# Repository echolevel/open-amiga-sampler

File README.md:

# OPEN AMIGA SAMPLER

## Open source schematics, parts lists and documentation for building a generic 8bit/mono Amiga parallel port sound sampler

Amiga parallel port sound samplers are simple hardware devices from the late 80s/early 90s which allowed users to digitally record audio to their home computer and represented a revolution in DIY music production. They were once cheap and ubiquitous, but they're increasingly expensive and hard to find as the popularity of retro computing continues to rise.

OAS is an open source PCB and case design for a cartridge-style mono sampler geared towards use with Soundtracker and Protracker-style software. It is easy to make, cheap to produce, and thanks to its built in preamp with hardware gain control it can deliver higher quality results than the average vintage sampler.

Please read the wiki for more information!

### [OAS Wiki Home](https://github.com/echolevel/open-amiga-sampler/wiki)

### Background

***
* [What are Amiga samplers?](https://github.com/echolevel/open-amiga-sampler/wiki/What-are-Amiga-samplers%3F)
* [Why build more?](https://github.com/echolevel/open-amiga-sampler/wiki/Why-build-more%3F)

### Development

***
* [How do they work?](https://github.com/echolevel/open-amiga-sampler/wiki/How-do-they-work%3F)
* [⚠️ WARNING](https://github.com/echolevel/open-amiga-sampler/wiki/%E2%9A%A0%EF%B8%8F-WARNING)
* [That WARNING sounds serious. How did you test your design without risking Amiga hardware?](https://github.com/echolevel/open-amiga-sampler/wiki/That-WARNING-sounds-serious.-How-did-you-test-your-design-without-risking-your-Amiga-hardware%3F)
* [Why is this sampler design mono, not stereo?](https://github.com/echolevel/open-amiga-sampler/wiki/Why-is-this-sampler-design-mono,-not-stereo%3F)
* [What's the aim in terms of quality and application?](https://github.com/echolevel/open-amiga-sampler/wiki/What's-the-aim-in-terms-of-quality-and-application%3F)
* [What about those edge cases? Who is OAS not aimed at?](https://github.com/echolevel/open-amiga-sampler/wiki/What-about-those-edge-cases%3F-Who-is-OAS-not-aimed-at%3F)
* [How compatible is OAS with existing software? (Work in progress, submissions welcome)](https://github.com/echolevel/open-amiga-sampler/wiki/How-compatible-is-OAS-with-existing-software%3F-(Work-in-progress,-submissions-welcome))
* [Current status](https://github.com/echolevel/open-amiga-sampler/wiki/Current-status)

### Production & Availability

***
* [Availability](https://github.com/echolevel/open-amiga-sampler/wiki/Availability)
* [DIY assembly](https://github.com/echolevel/open-amiga-sampler/wiki/DIY-assembly)

### Appendices

***
* [Appendix A: Sample rates deep-dive](https://github.com/echolevel/open-amiga-sampler/wiki/Appendix-A:-Sample-rates-deep-dive)
* [Appendix B: Sampling duration deep-dive](https://github.com/echolevel/open-amiga-sampler/wiki/Appendix-B:-Sampling-duration-deep-dive)

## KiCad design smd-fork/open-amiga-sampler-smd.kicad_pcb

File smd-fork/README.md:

# OPEN AMIGA SAMPLER

## Overview

Here you can find the schematic and a PCB layout for Open Amiga Sampler in KiCAD format. Additionally, the schematic is available as a PDF.

The design consists of an inverting opamp circuit with variable gain which feeds an ADC. The DB25's strobe pin is connected to the ADC and initiates a conversion when it goes low. The ADC's outputs are connected to the data pins of a DB25 connector, which also provides power and ground. 

## BOM

* 1x Maxim ADC0820CCM+ (SOIC-20 Package) - mouser P/N  700-ADC0820CCM
* 1x Microchip MCP6001UT-I/OT (SOT-23-5 package) - mouser P/N 579-MCP6001UT-I/OT (The U variant is important as it has a different pin layout to the 6001T in the same package)
* 1x DB25 plug connector
* 2x RCA receptacles
* 1x 0805 330ohm resistor 
* 5x 0805 1kohm resistors
* 1x 10kohm exponential potentimeter
* 1x 4x5.3mm 47uF electrolytic capacitor
* 2x 10uf Tantalum Case A or 1206 capacitors
* 2x 0805 0.1uf capacitors

### Substitutions

The Maxim ADC0820CCM+ is pin compatible with the TI part with the same part number and package. The Maxim part is preferred as it's a better spec but the TI part can easily be substituted as the Maxim is pin-compatible.

The 10kohm potentiometer will give between 1x and 10x gain. A larger potentiometer can be substituted to enable a large maxium gain. The RCA receptacles can be replaced by a stereo jack receptacle if preferred. It is likely that both ICs could be substituted for similar chips with identical pinouts, but these are the models that we have tested and confirmed to work.

The 47uF electrolytic can be substituted for a taller one up to 5.8mm if using a standard grey DB25 shell or taller if using a bigger (e.g. 3D printed) case 

## Soldering

All on board components are surface mount but nothing smaller than 0805 and should be relatively easy to solder even for someone with a good base level of soldering and a bit of practice. The MCP6001 is a SOT-23-5 with a ~1mm pitch and represents the smallest component on the board. the Pot and RCA receptacles can be soldered with wire leads from the through hole pads

## Case

This board is intended to fit inside a standard DB25 D-Sub shell. (a regular common grey one) but due to it's small size, a larger enclosure can also be used and a custom 3D printed one may get produced as well.

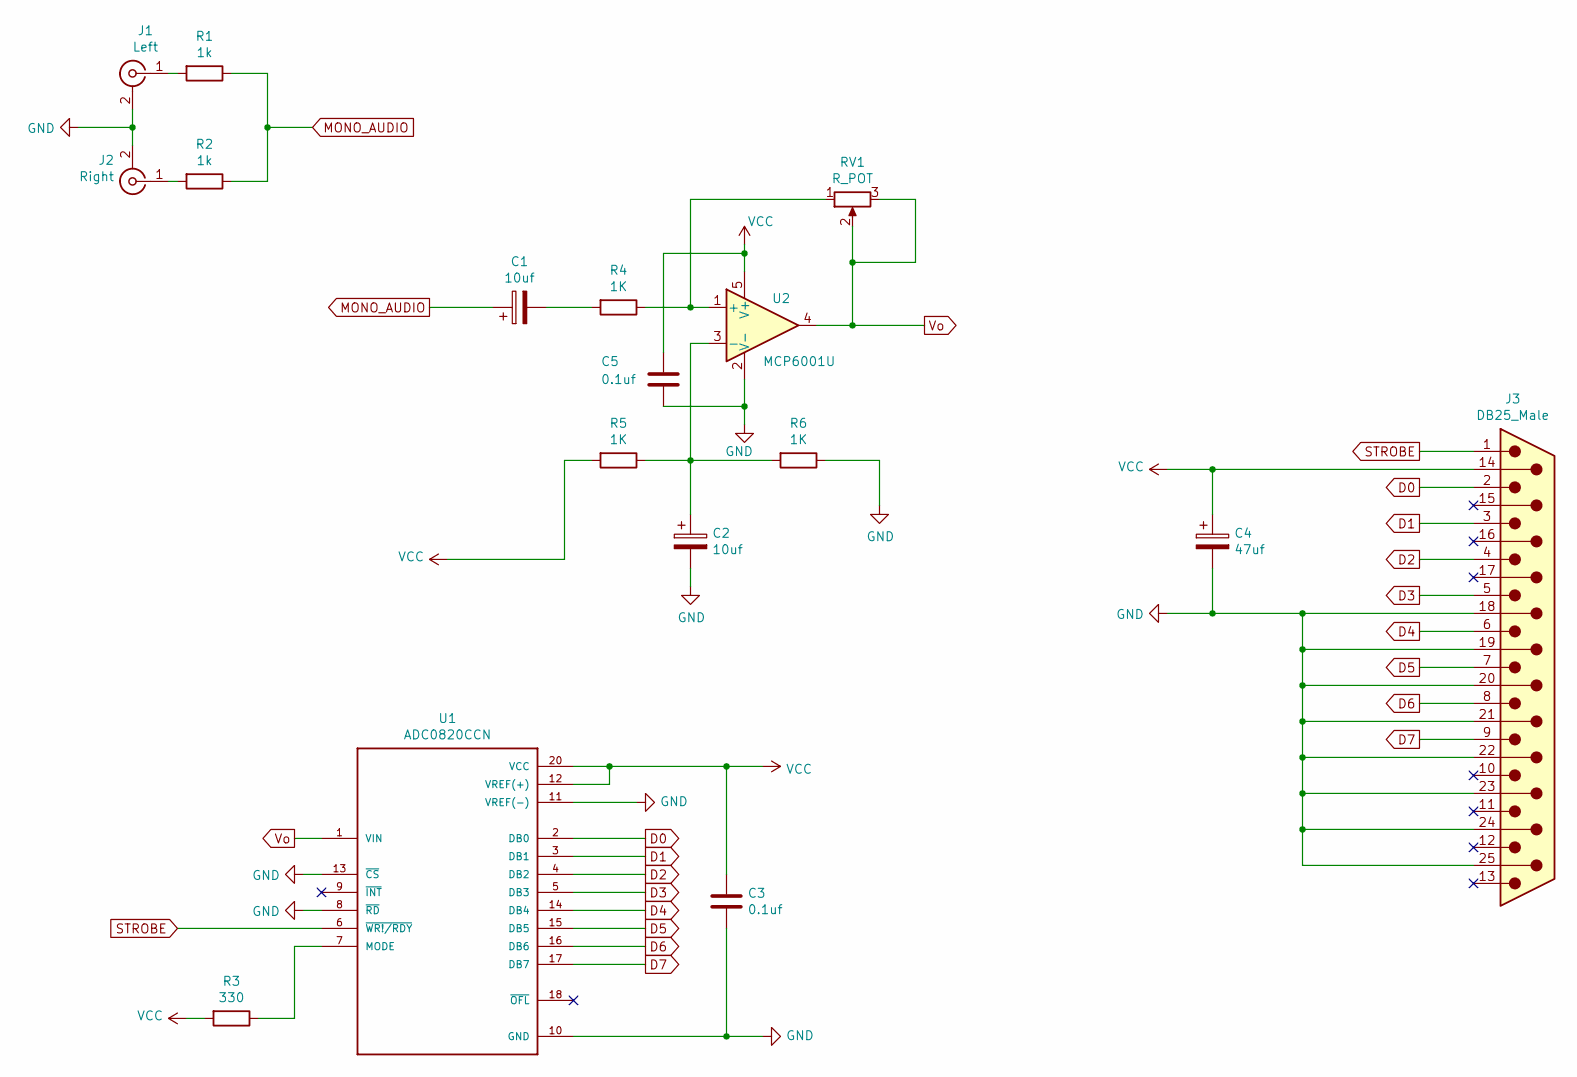
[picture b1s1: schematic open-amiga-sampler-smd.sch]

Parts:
C1, C2: 10uf; CP_EIA-3216-18_Kemet-A_Pad1.58x1.35mm_HandSolder
C3, C5: 0.1uf; C_0805_2012Metric_Pad1.15x1.40mm_HandSolder
C4: 47uf; CP_Elec_4x5.3
J1: Left; PinHeader_1x02_P2.00mm_Vertical
J2: Right; PinHeader_1x02_P2.00mm_Vertical
J3: DB25_Male; DSUB-25_Male_EdgeMount_P2.77mm
R1, R2: 1k; R_0805_2012Metric_Pad1.15x1.40mm_HandSolder
R3: 330; R_0805_2012Metric_Pad1.15x1.40mm_HandSolder
R4, R5, R6: 1K; R_0805_2012Metric_Pad1.15x1.40mm_HandSolder
RV1: R_POT; PinHeader_1x03_P2.00mm_Vertical
U1: ADC0820CCN; SOIC-20W_7.5x12.8mm_P1.27mm
U2: MCP6001U; SOT-23-5

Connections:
D0: J3.2, U1.2 (DB0)
D1: J3.3, U1.3 (DB1)
D2: J3.4, U1.4 (DB2)
D3: J3.5, U1.5 (DB3)
D4: J3.6, U1.14 (DB4)
D5: J3.7, U1.15 (DB5)
D6: J3.8, U1.16 (DB6)
D7: J3.9, U1.17 (DB7)
GND: C2.2, C3.2, C4.2, C5.2, J1.2 (Ext), J2.2 (Ext), J3.18, J3.19, J3.20, J3.21, J3.22, J3.23, J3.24, J3.25, R6.1, U1.8 (~RD~), U1.10 (GND), U1.11 (VREF(-)), U1.13 (~CS~), U2.2 (V-)
MONO_AUDIO: C1.1, R1.1, R2.1
unnamed: C1.2, R4.2
unnamed: C2.1, R5.1, R6.2, U2.3 (-)
unnamed: J1.1 (In), R1.2
unnamed: J2.1 (In), R2.2
unnamed: R3.1, U1.7 (MODE)
unnamed: R4.1, RV1.1, U2.1 (+)
STROBE: J3.1, U1.6 (~WR!/RDY~)
VCC: C3.1, C4.1, C5.1, J3.14, R3.2, R5.2, U1.12 (VREF(+)), U1.20 (VCC), U2.5 (V+)
Vo: RV1.2, RV1.3, U1.1 (VIN), U2.4

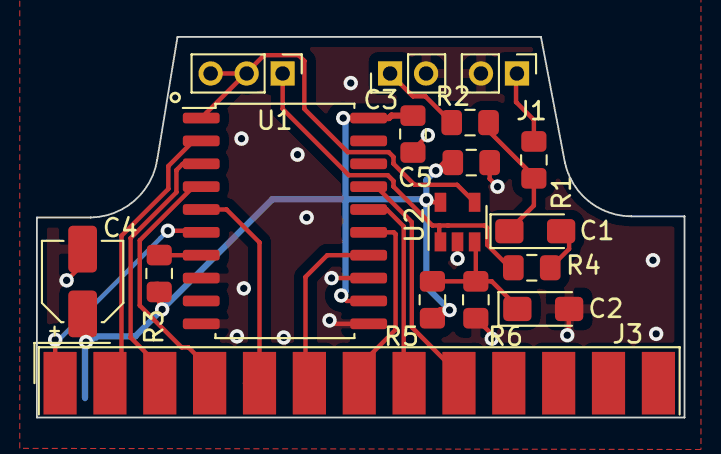
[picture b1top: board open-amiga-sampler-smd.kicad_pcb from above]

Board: 2 copper layers, 36.0 x 21.1 mm, 17 parts (0 on the bottom side), 19 nets.

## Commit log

2020-07-03 initial docs
    initial docs
2020-07-03 update
    update
2020-07-03 upd
    upd
2020-07-05 First go at a schematic
2020-07-05 Added gain potentiometer
2020-07-05 edited readme
    edited readme
2020-07-07 Fixed + and - on the op amp being the wrong way
2020-07-08 docs
    docs
2020-07-08 Added stereo mix circuit
2020-07-12 Initial go at a PCB layout.
2020-07-12 Missing bits for PCB layout
2020-07-13 Fixed op amp circuit
2020-07-13 Added some images and PDF schematic
2020-07-18 Initial case SCAD file
2020-07-24 A few small tweaks
2020-07-24 Short readme for the KiCAD files
2020-07-24 Another small fix
2020-07-24 Removed unfinished case design and moved schematic PDF
2020-07-24 added pic
2020-07-24 Renamed schematic PDF and mentioned it in the readme
2020-07-26 Latest prototype case, still experimenting
2020-07-28 SMD-branch created
    initial pass on SMD-branch. second pass layout done.
    TODO: add casing and board-mount pot considerations.
    consider housing in a standard DB-shell
2020-07-28 Snap fit attempt 2
2020-07-29 tidied up positions and silkscreen
    Added new nilkscreen items and adjusted positions of a few components to avoid courtyard violations in DRC. upgraded VCC trace to be thicker
2020-07-29 updated gerber plot
2020-07-29 VCC improvements
    changed mailn bulk bypass cap to electrolytic. moved C3 to close to U1 Vcc. tweaked Vcc traces for better path. Silkscreen++
2020-07-30 fixed unconnected grounds
2020-07-30 updated gerbers
2020-07-30 uhhh some changes to the PCB
2020-07-30 Latest snap-fit design
2020-07-31 re-did board outline to (maybe) actually fit
    Using an accutare 3D model for a shell the board has been re-jigged to fit. still not tested against a real one though
2020-07-31 added drill file to gerbers
2020-08-04 Added Teensy tester code and some documentation
    Added Teensy tester code and some documentation
2020-08-04 Update README.md
    updated Teensy docs
2020-08-04 Update README.md
    updated docs
2020-08-04 Update TeensyAmigaSamplerTester.ino
    tidied up Teensy code
2020-08-04 added stl files
2020-08-07 Yet another snapfit redesign
2020-08-09 updates to case stls
    minor PCB tweaks
2020-08-13 minor trace layout improvments
    Rev 2
2020-08-13 Yet another prototype case
2020-08-16 Another one
2020-08-25 Added case stl files
2020-08-25 Working case design
2020-08-25 Moved Classic Edition files to their own dir
2020-08-25 Placeholder docs
2020-08-30 Made case and phono distance wider, added built in spacer for pot
2020-09-09 rev 2
    case files and board tweaks
2021-01-17 Updated silk screen text
2021-01-29 Update README.md
    Broke the readme up into wiki entries and replaced it with an overview and TOC
